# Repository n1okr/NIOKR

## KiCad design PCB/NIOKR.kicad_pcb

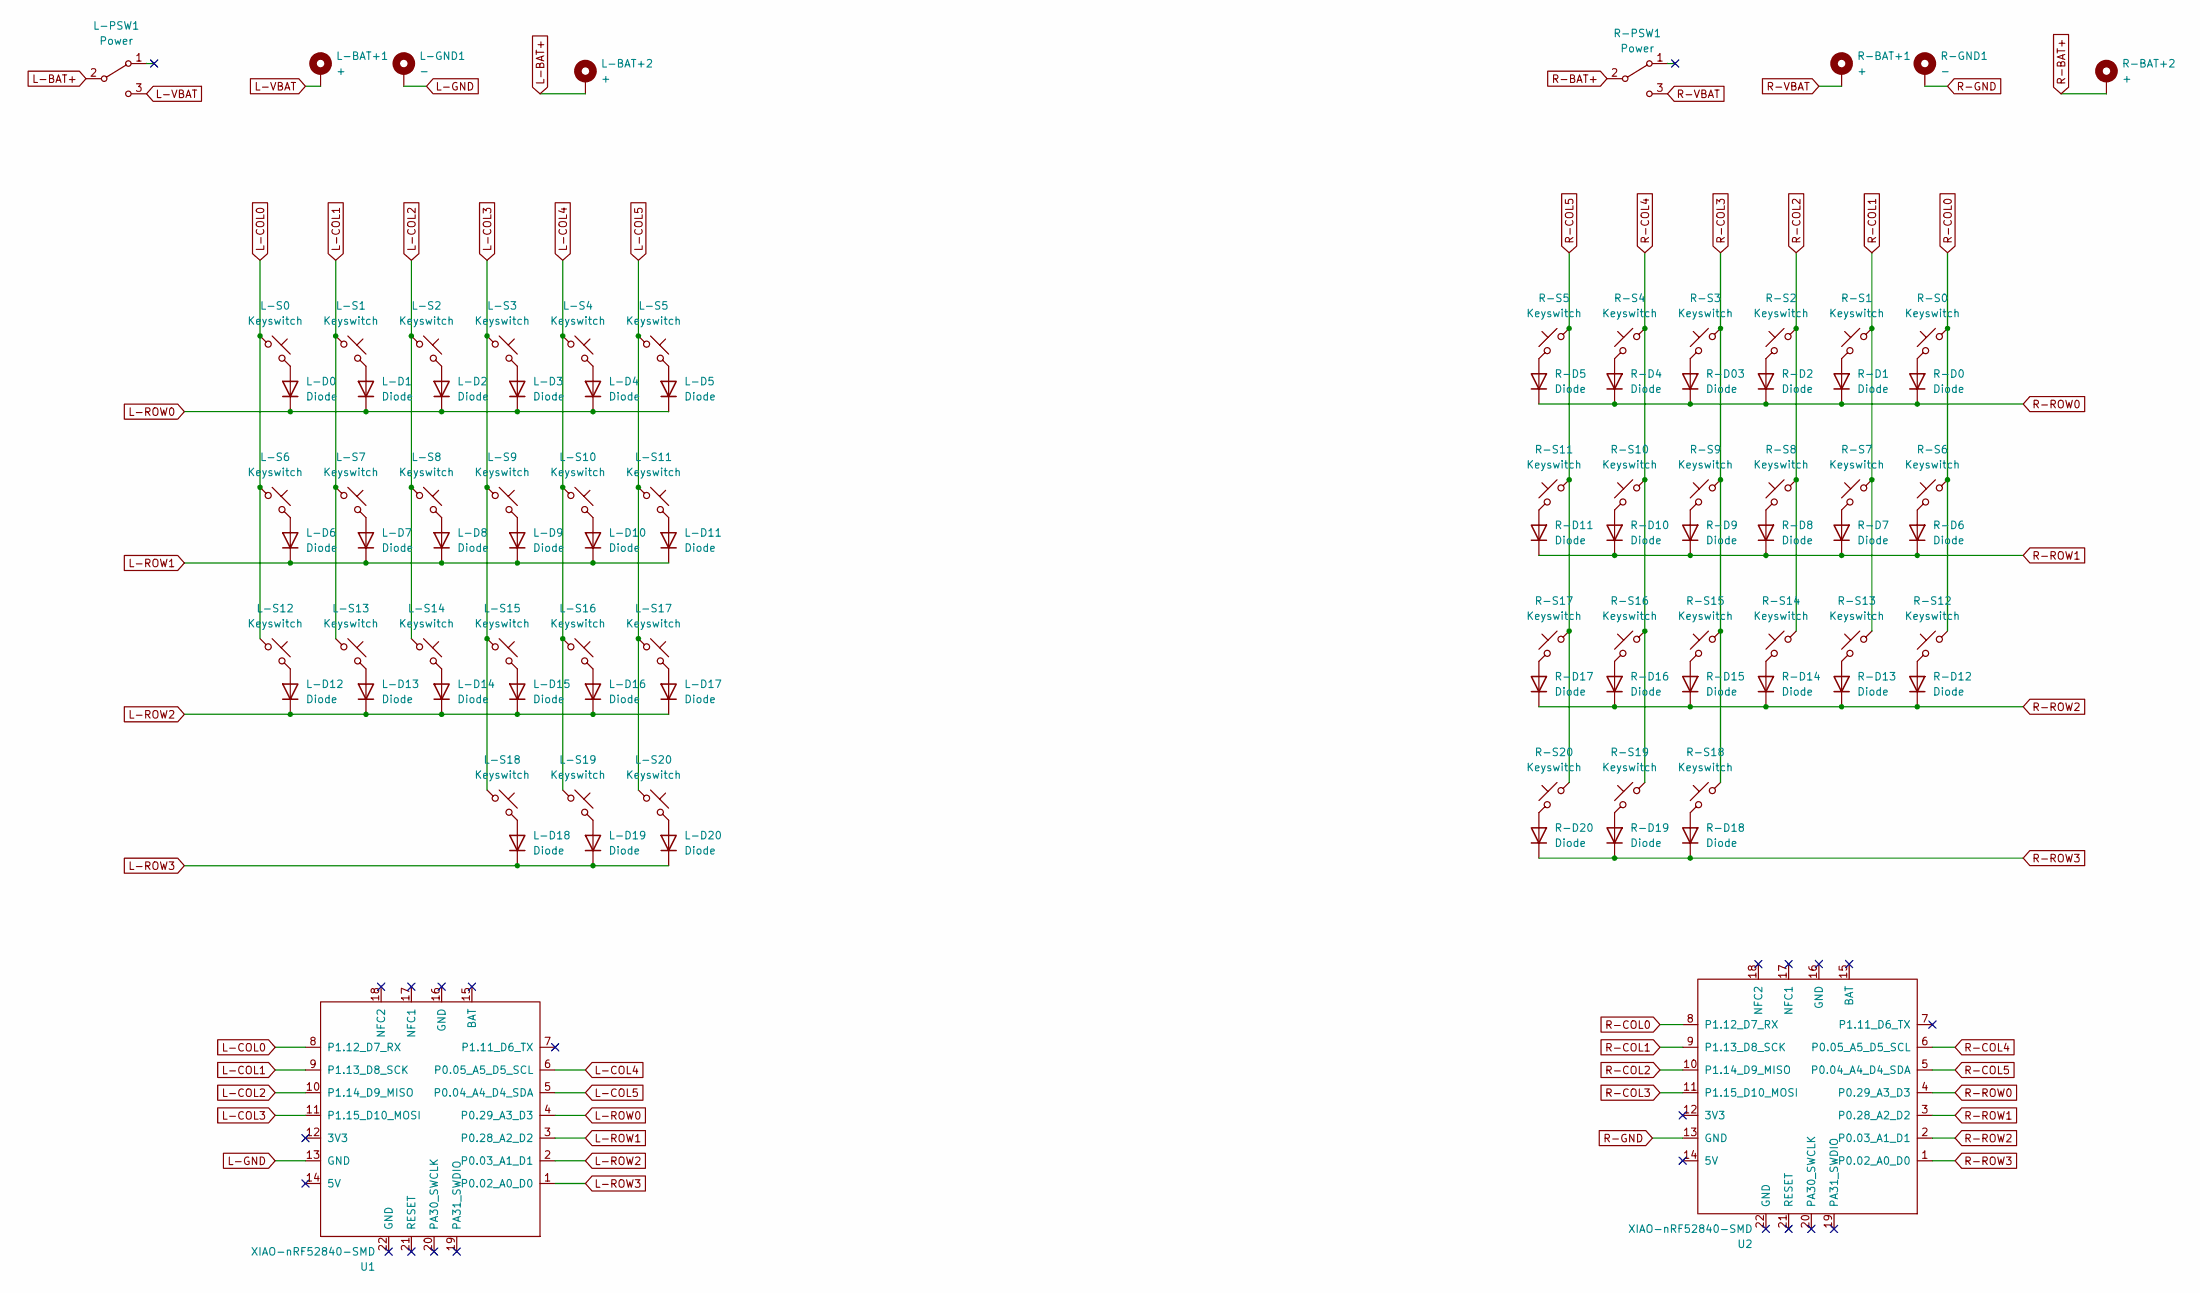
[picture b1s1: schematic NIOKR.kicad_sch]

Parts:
L-BAT+1, L-BAT+2: +; BatteryPad
L-D0, L-D1, L-D2, L-D3, L-D4, L-D5, L-D6, L-D7, L-D8, L-D9, L-D10, L-D11, L-D12, L-D13, L-D14, L-D15, L-D16, L-D17, L-D18, L-D19, L-D20: Diode; Diode_SOD123
L-GND1: -; BatteryPad
L-PSW1: Power; MSK12C02
L-S0, L-S1, L-S2, L-S3, L-S4, L-S5, L-S6, L-S7, L-S8, L-S9, L-S10, L-S11, L-S12, L-S13, L-S14, L-S15, L-S16, L-S17, L-S18, L-S19, L-S20: Keyswitch; keyswitch_choc12-topor
R-BAT+1, R-BAT+2: +; BatteryPad
R-D0, R-D1, R-D2, R-D03, R-D4, R-D5, R-D6, R-D7, R-D8, R-D9, R-D10, R-D11, R-D12, R-D13, R-D14, R-D15, R-D16, R-D17, R-D18, R-D19, R-D20: Diode; Diode_SOD123
R-GND1: -; BatteryPad
R-PSW1: Power; MSK12C02
R-S0, R-S1, R-S2, R-S3, R-S4, R-S5, R-S6, R-S7, R-S8, R-S9, R-S10, R-S11, R-S12, R-S13, R-S14, R-S15, R-S16, R-S17, R-S18, R-S19, R-S20: Keyswitch; keyswitch_choc12-topor
U1, U2: XIAO-nRF52840-SMD; XIAO-nRF52840-cutout-plain

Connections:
L-BAT+: L-BAT+2.1 (BAT+), L-PSW1.2 (B)
L-COL0: L-S0.1, L-S6.1, L-S12.1, U1.8 (P1.12_D7_RX)
L-COL1: L-S1.1, L-S7.1, L-S13.1, U1.9 (P1.13_D8_SCK)
L-COL2: L-S2.1, L-S8.1, L-S14.1, U1.10 (P1.14_D9_MISO)
L-COL3: L-S3.1, L-S9.1, L-S15.1, L-S18.1, U1.11 (P1.15_D10_MOSI)
L-COL4: L-S4.1, L-S10.1, L-S16.1, L-S19.1, U1.6 (P0.05_A5_D5_SCL)
L-COL5: L-S5.1, L-S11.1, L-S17.1, L-S20.1, U1.5 (P0.04_A4_D4_SDA)
L-GND: L-GND1.1 (GND), U1.13 (GND)
L-ROW0: L-D0.1 (K), L-D1.1 (K), L-D2.1 (K), L-D3.1 (K), L-D4.1 (K), L-D5.1 (K), U1.4 (P0.29_A3_D3)
L-ROW1: L-D6.1 (K), L-D7.1 (K), L-D8.1 (K), L-D9.1 (K), L-D10.1 (K), L-D11.1 (K), U1.3 (P0.28_A2_D2)
L-ROW2: L-D12.1 (K), L-D13.1 (K), L-D14.1 (K), L-D15.1 (K), L-D16.1 (K), L-D17.1 (K), U1.2 (P0.03_A1_D1)
L-ROW3: L-D18.1 (K), L-D19.1 (K), L-D20.1 (K), U1.1 (P0.02_A0_D0)
L-VBAT: L-BAT+1.1 (BAT+), L-PSW1.3 (C)
unnamed: L-D0.2 (A), L-S0.2
unnamed: L-D1.2 (A), L-S1.2
unnamed: L-D2.2 (A), L-S2.2
unnamed: L-D3.2 (A), L-S3.2
unnamed: L-D4.2 (A), L-S4.2
unnamed: L-D5.2 (A), L-S5.2
unnamed: L-D6.2 (A), L-S6.2
unnamed: L-D7.2 (A), L-S7.2
unnamed: L-D8.2 (A), L-S8.2
unnamed: L-D9.2 (A), L-S9.2
unnamed: L-D10.2 (A), L-S10.2
unnamed: L-D11.2 (A), L-S11.2
unnamed: L-D12.2 (A), L-S12.2
unnamed: L-D13.2 (A), L-S13.2
unnamed: L-D14.2 (A), L-S14.2
unnamed: L-D15.2 (A), L-S15.2
unnamed: L-D16.2 (A), L-S16.2
unnamed: L-D17.2 (A), L-S17.2
unnamed: L-D18.2 (A), L-S18.2
unnamed: L-D19.2 (A), L-S19.2
unnamed: L-D20.2 (A), L-S20.2
unnamed: R-D0.2 (A), R-S0.2
unnamed: R-D1.2 (A), R-S1.2
unnamed: R-D2.2 (A), R-S2.2
unnamed: R-D03.2 (A), R-S3.2
unnamed: R-D4.2 (A), R-S4.2
unnamed: R-D5.2 (A), R-S5.2
unnamed: R-D6.2 (A), R-S6.2
unnamed: R-D7.2 (A), R-S7.2
unnamed: R-D8.2 (A), R-S8.2
unnamed: R-D9.2 (A), R-S9.2
unnamed: R-D10.2 (A), R-S10.2
unnamed: R-D11.2 (A), R-S11.2
unnamed: R-D12.2 (A), R-S12.2
unnamed: R-D13.2 (A), R-S13.2
unnamed: R-D14.2 (A), R-S14.2
unnamed: R-D15.2 (A), R-S15.2
unnamed: R-D16.2 (A), R-S16.2
unnamed: R-D17.2 (A), R-S17.2
unnamed: R-D18.2 (A), R-S18.2
unnamed: R-D19.2 (A), R-S19.2
unnamed: R-D20.2 (A), R-S20.2
R-BAT+: R-BAT+2.1 (BAT+), R-PSW1.2 (B)
R-COL0: R-S0.1, R-S6.1, R-S12.1, U2.8 (P1.12_D7_RX)
R-COL1: R-S1.1, R-S7.1, R-S13.1, U2.9 (P1.13_D8_SCK)
R-COL2: R-S2.1, R-S8.1, R-S14.1, U2.10 (P1.14_D9_MISO)
R-COL3: R-S3.1, R-S9.1, R-S15.1, R-S18.1, U2.11 (P1.15_D10_MOSI)
R-COL4: R-S4.1, R-S10.1, R-S16.1, R-S19.1, U2.6 (P0.05_A5_D5_SCL)
R-COL5: R-S5.1, R-S11.1, R-S17.1, R-S20.1, U2.5 (P0.04_A4_D4_SDA)
R-GND: R-GND1.1 (GND), U2.13 (GND)
R-ROW0: R-D0.1 (K), R-D1.1 (K), R-D2.1 (K), R-D03.1 (K), R-D4.1 (K), R-D5.1 (K), U2.4 (P0.29_A3_D3)
R-ROW1: R-D6.1 (K), R-D7.1 (K), R-D8.1 (K), R-D9.1 (K), R-D10.1 (K), R-D11.1 (K), U2.3 (P0.28_A2_D2)
R-ROW2: R-D12.1 (K), R-D13.1 (K), R-D14.1 (K), R-D15.1 (K), R-D16.1 (K), R-D17.1 (K), U2.2 (P0.03_A1_D1)
R-ROW3: R-D18.1 (K), R-D19.1 (K), R-D20.1 (K), U2.1 (P0.02_A0_D0)
R-VBAT: R-BAT+1.1 (BAT+), R-PSW1.3 (C)

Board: 2 copper layers, 102 parts (44 on the bottom side), 68 nets, no tracks yet.

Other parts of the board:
mbites1, mbites2, mbites3, mbites4, mbites5, mbites6, mbites7, mbites8: mousebites 2mm; mousebites_0.6-0.4-topor

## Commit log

2025-03-02 minimal-updates
2025-03-06 houdini routing
2025-03-06 growth
2025-03-25 current
2025-04-12 thumbs and footprints
2025-04-27 wip v2
2025-05-06 Pipeline_preparation
2025-05-07 wip pattern
2025-05-11 algo almost done + chocv1
2025-05-12 choc1 updates
2025-05-19 houdini pattern detangled for choc12
2025-08-04 latest
